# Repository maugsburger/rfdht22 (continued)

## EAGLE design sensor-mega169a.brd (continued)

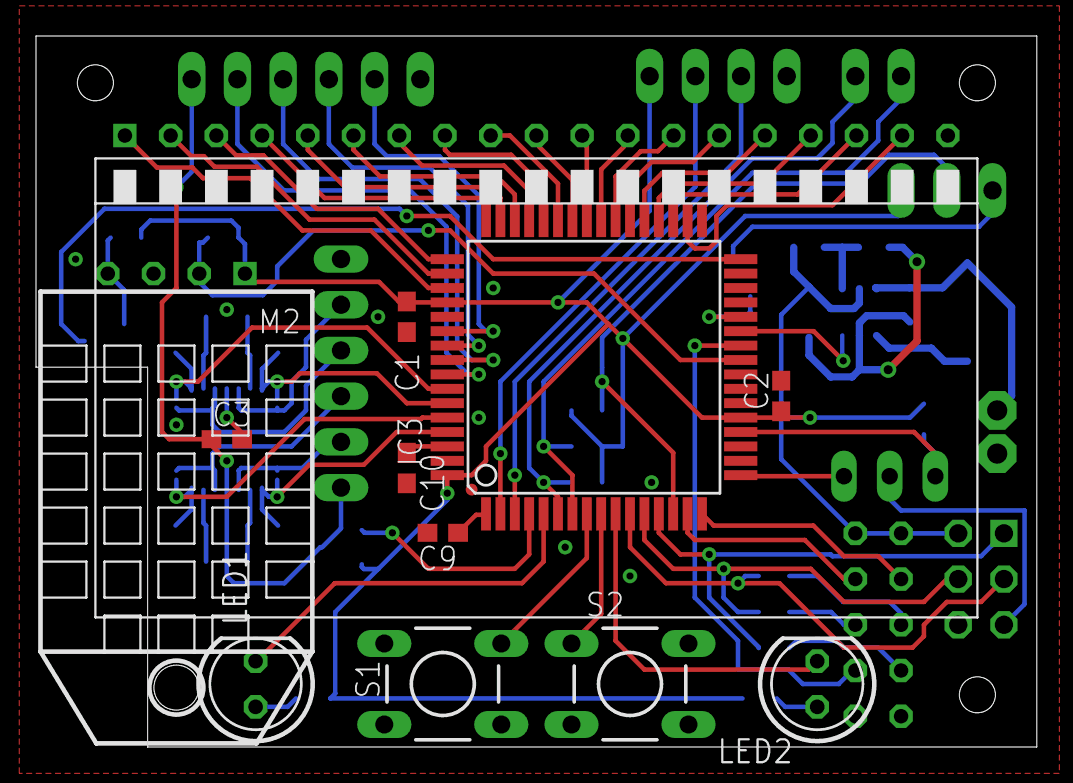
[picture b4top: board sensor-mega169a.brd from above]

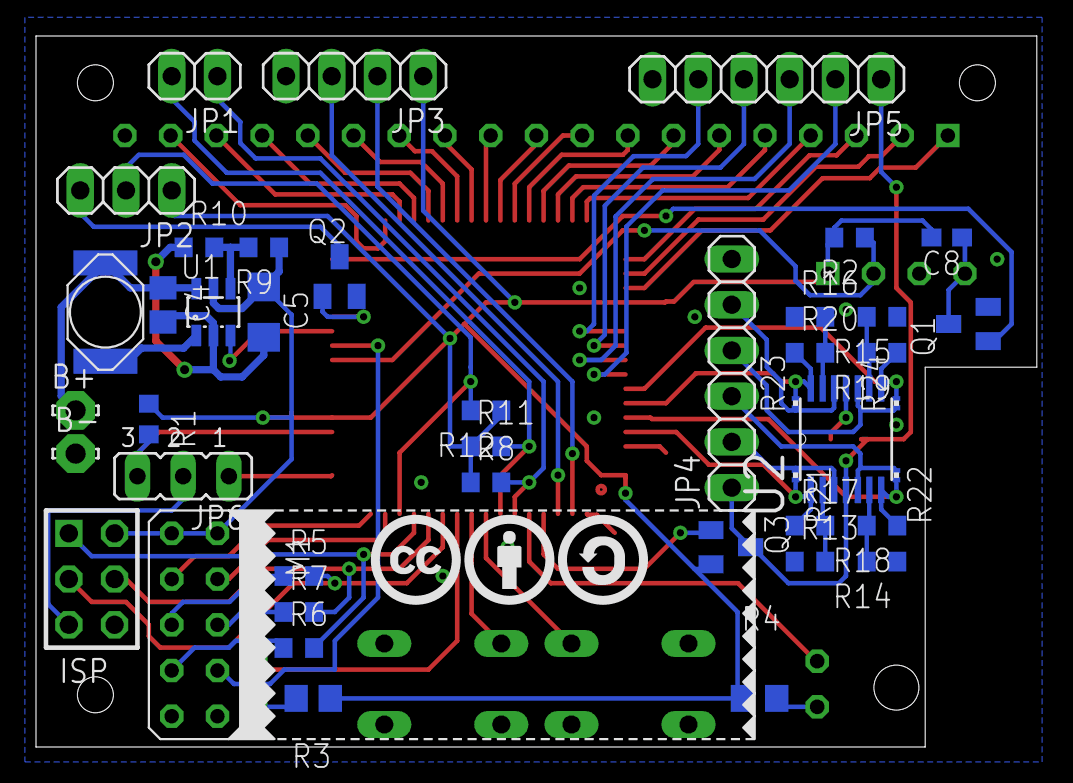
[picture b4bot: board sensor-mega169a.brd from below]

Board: 2 copper layers, 55.6 x 39.5 mm, 59 parts (46 on the bottom side), 72 nets.

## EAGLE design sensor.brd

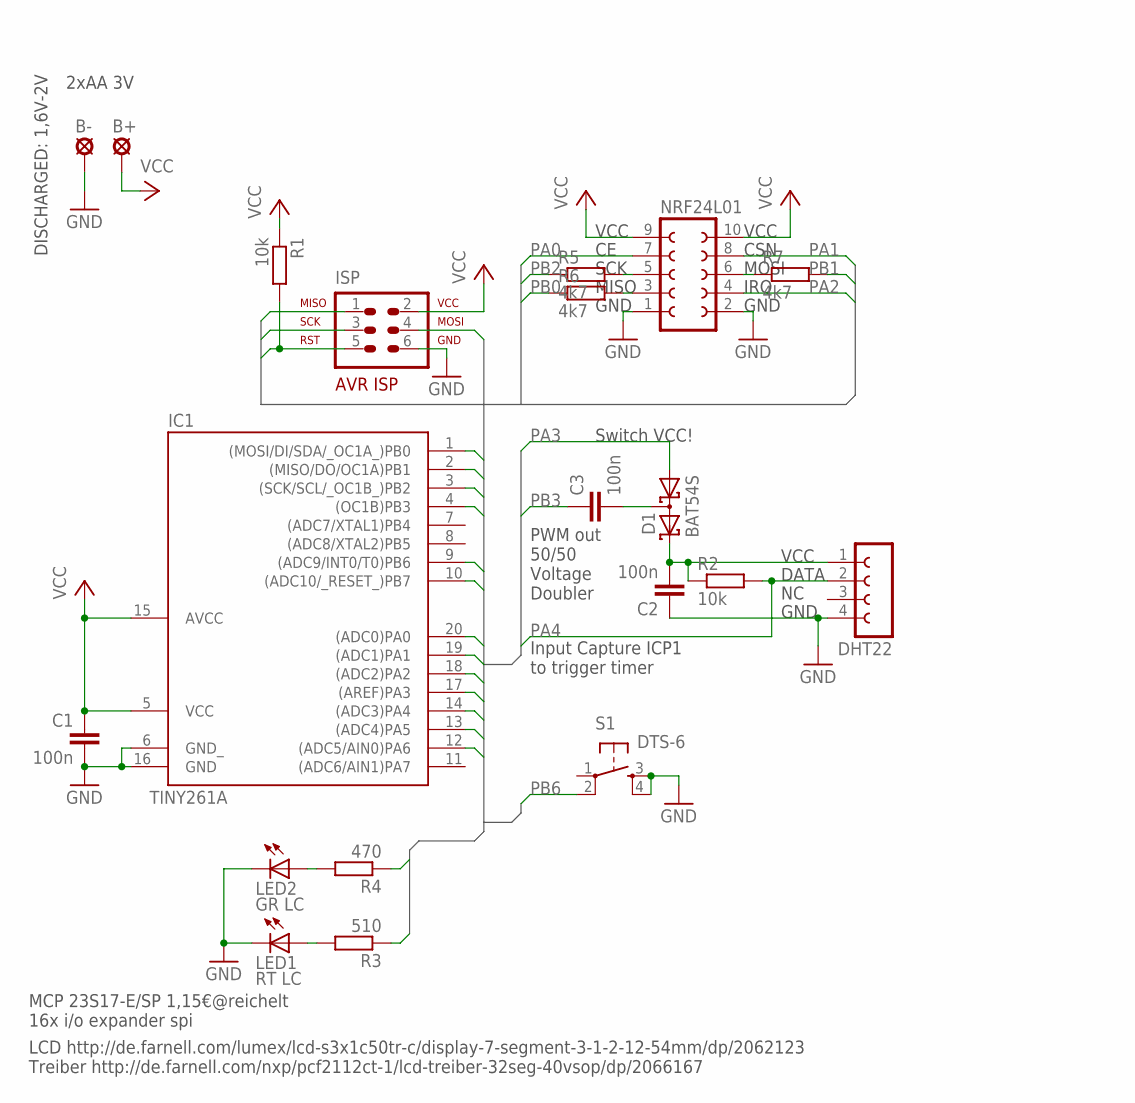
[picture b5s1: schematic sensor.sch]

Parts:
B+: LSP11
B-: LSP11
C1, C2, C3: 100n; C0805
D1: BAT54S; SOT23
DHT22: FE04-1
IC1: TINY261A; DIL20
ISP: ML6; AVR-ISP-6
LED1: RT LC; LED5MM
LED2: GR LC; LED5MM
NRF24L01: FE05-2
R1, R2: 10k; R0805
R3: 510; R0805
R4: 470; R0805
R5, R6, R7: 4k7; 0207/7
S1: DTS-6

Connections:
DHTVCC: C2.2, D1.2 (C2), DHT22.1, R2.1
GND: B-.MP, C1.2, C2.1, DHT22.4, IC1.6 (GND_), IC1.16 (GND), ISP.6, LED1.K (C), LED2.K (C), NRF24L01.1, NRF24L01.2, S1.3, S1.4
unnamed: LED2.A, R4.2
unnamed: C3.2, D1.3 (C1A2)
unnamed: NRF24L01.5, R5.2
unnamed: NRF24L01.3, R6.2
unnamed: NRF24L01.6, R7.1
unnamed: LED1.A, R3.2
PA0: IC1.20 ((ADC0)PA0), NRF24L01.7
PA1: IC1.19 ((ADC1)PA1), NRF24L01.8
PA2: IC1.18 ((ADC2)PA2), NRF24L01.4
PA3: D1.1 (A1), IC1.17 ((AREF)PA3)
PA4: DHT22.2, IC1.14 ((ADC3)PA4), R2.2
PA5: IC1.13 ((ADC4)PA5), R3.1
PA6: IC1.12 ((ADC5/AIN0)PA6), R4.1
PB0: IC1.1 ((MOSI/DI/SDA/_OC1A_)PB0), ISP.4, R6.1
PB1: IC1.2 ((MISO/DO/OC1A)PB1), ISP.1, R7.2
PB2: IC1.3 ((SCK/SCL/_OC1B_)PB2), ISP.3, R5.1
PB3: C3.1, IC1.4 ((OC1B)PB3)
PB6: IC1.9 ((ADC9/INT0/T0)PB6), S1.2
PB7: IC1.10 ((ADC10/_RESET_)PB7), ISP.5, R1.2
VCC: B+.MP, C1.1, IC1.5 (VCC), IC1.15 (AVCC), ISP.2, NRF24L01.9, NRF24L01.10, R1.1

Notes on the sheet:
VCC
SCK
GND
IRQ
MISO
MOSI
CSN
2xAA 3V
DATA
DISCHARGED: 1,6V-2V
Input Capture ICP1 to trigger timer
PWM out 50/50 Voltage Doubler
Switch VCC!
LCD http://de.farnell.com/lumex/lcd-s3x1c50tr-c/display-7-segment-3-1-2-12-54mm/dp/2062123 Treiber http://de.farnell.com/nxp/pcf2112ct-1/lcd-treiber-32seg-40vsop/dp/2066167
MCP 23S17-E/SP 1,15€@reichelt 16x i/o expander spi

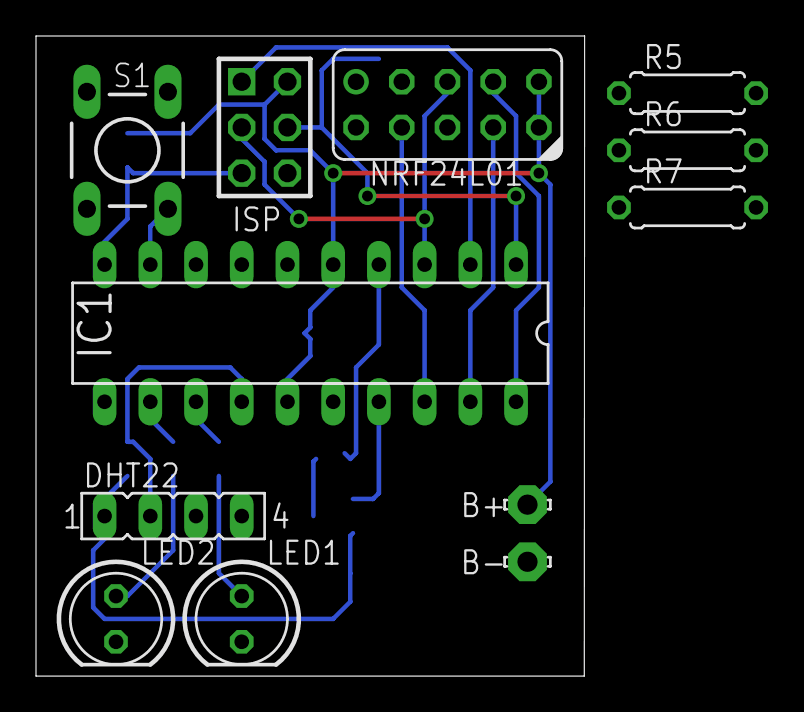
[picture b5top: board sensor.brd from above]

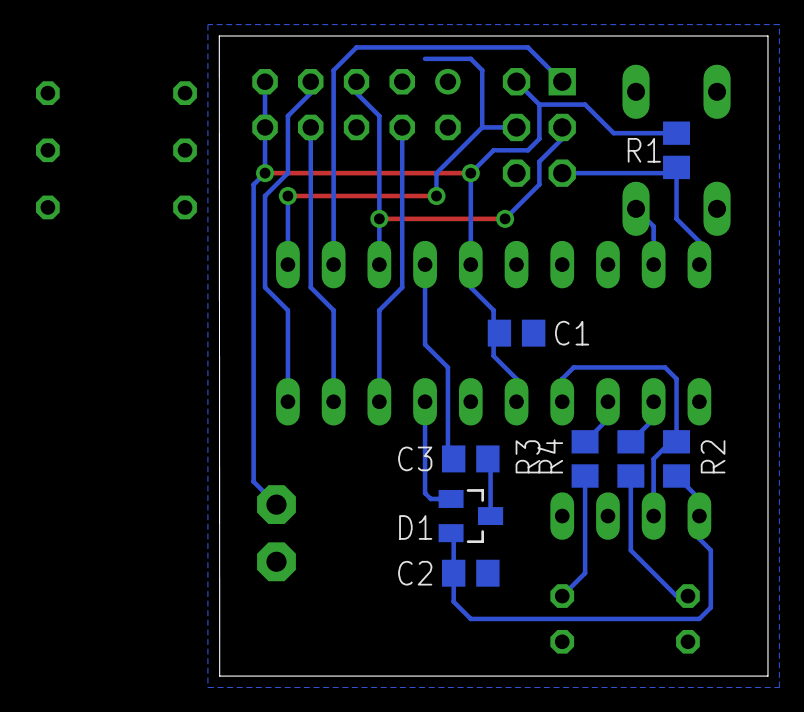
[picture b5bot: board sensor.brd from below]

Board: 2 copper layers, 30.5 x 35.6 mm, 20 parts (8 on the bottom side), 22 nets.

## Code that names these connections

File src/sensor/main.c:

/*
 * Copyright 2013 Moritz Augsburger <code@moritz.augsburger.name>
 *
 * This file is part of rfdht22.
 *
 * rfdht22 is free software: you can redistribute it and/or modify
 * it under the terms of the GNU General Public License as published by
 * the Free Software Foundation, either version 3 of the License, or
 * (at your option) any later version.
 *
 * Foobar is distributed in the hope that it will be useful,
 * but WITHOUT ANY WARRANTY; without even the implied warranty of
 * MERCHANTABILITY or FITNESS FOR A PARTICULAR PURPOSE.  See the
 * GNU General Public License for more details.
 *
 * You should have received a copy of the GNU General Public License
 * along with Foobar.  If not, see <http://www.gnu.org/licenses/>.
 *
 */

#include "main.h"
volatile uint8_t isr_interval;

void dhtpwr_on() {
        // PB2 == OC0A
        TCCR0A =    (1<<WGM01) | (1<<WGM00) | //
                    (1<<COM0A1); // Clear OC0A on match, set at TOP
        TCCR0B = (0<<CS01) | (1<<CS00); // no prescaling
        OCR0A = 127;

        // PB2 und PB0 Ausgang
        DDRB |= (1<<PB2) | (1<<PB0);
        // PB0 VCC für Doubler
        PORTB |= (1<<PB0);
}

void dhtpwr_off() {
        // PB2 und PB1 kein Ausgang
        PORTB &= ~(1<<PB0);
        DDRB &= ~(1<<PB2) | (1<<PB0);
        TCCR0A = (0<<WGM01) | (0<<WGM00);
        TCCR0B = (0<<CS01) | (0<<CS00);     // stop counter
}

void sleep_time(uint8_t sleepmode, uint8_t intervals ) {
    wdt_reset();
    isr_interval = intervals;
    WDTCR = (1<<WDIF) | (1<<WDIE) | (1<<WDP3) | (1<<WDP0);
    while(isr_interval > 0) {
        set_sleep_mode(sleepmode);
        sleep_mode();
    }
    wdt_disable();
}

void blink(uint8_t c) {
    do {
        PORTA |= (1<<PA0);
        _delay_ms(100);
        PORTA &= ~(1<<PA0);
        _delay_ms(100);
        c--;
    } while (c>0);
    _delay_ms(500);
}

int main (void) {

    uint16_t temperature;
    uint16_t humidity;
    uint8_t  dht22res;

    uint8_t payload[wl_module_PAYLOAD];		//Array for Payload
	uint8_t k;
	
	wl_module_init();	    //initialise nRF24L01+ Module
	_delay_ms(50);		    //wait for nRF24L01+ Module
    wl_module_tx_config(wl_module_TX_NR_0);		//Config Module

 //   dhtpwr(true);

    PORTA = (1<<PA1) | (1<<PA0);
    DDRA  = (1<<PA0) | (1<<PA1);
    _delay_ms(500);

    while(1) {
        // measure
        PORTA = (1<<PA1);
        dht22res = dhtmeasure(&temperature, &humidity );
        PORTA = 0;

        for (k=0; k<=wl_module_PAYLOAD-1; k++) {
            payload[k] = k;
        }
        payload[0] = dht22res;
        payload[1] = temperature;
        payload[2] = (temperature>>8);
        payload[3] = humidity;
        payload[4] = (humidity>>8);

        sei();
        wl_module_send(payload,wl_module_PAYLOAD);
        _delay_ms(5000);

    }
}

ISR(WDT_OVERFLOW_vect) {
    isr_interval--; 
}

#if defined(__AVR_ATtiny2313__) || defined(__AVR_ATtiny2313A__)
ISR(INT0_vect) {
#endif
    uint8_t status;

    // Read wl_module status
    wl_module_CSN_lo;                               // Pull down chip select
    status = spi_fast_shift(NOP);					// Read status register
    wl_module_CSN_hi;                               // Pull up chip select

    // Package has been sent
    if (status & (1<<TX_DS)) {
        wl_module_config_register(STATUS, (1<<TX_DS));	//Clear Interrupt Bit
        PTX=0;
    }

    // IRQ: Package has not been sent, send again
    if (status & (1<<MAX_RT)) {
        wl_module_config_register(STATUS, (1<<MAX_RT));	// Clear Interrupt Bit
        wl_module_CE_hi;								// Start transmission
        _delay_us(10);								
        wl_module_CE_lo;
    }

    //TX_FIFO Full <-- this is not an IRQ
    if (status & (1<<TX_FULL)) {
        wl_module_CSN_lo;                               // Pull down chip select
        spi_fast_shift(FLUSH_TX);						// Flush TX-FIFO
        wl_module_CSN_hi;                               // Pull up chip select
    }
}
/*
static volatile uint8_t zahl[5];

        asm (   "sec"       "\n\t"
                "rol %0"    "\n\t"
                "rol %1"    "\n\t"
                "rol %2"    "\n\t"
                "rol %3"    "\n\t"
                "rol %4"
                :"+r"( zahl[4] ),
                 "+r"( zahl[3] ),
                 "+r"( zahl[2] ),
                 "+r"( zahl[1] ),
                 "+r"( zahl[0] ) );

=> 26 zyklen
*/

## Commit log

2013-06-21 started project
2013-06-25 dht22 measurement and serial output working
2013-06-25 nrf24l01 code from http://www.mikrocontroller.net/articles/NRF24L01_Tutorial
2013-06-25 import lcd lib from http://homepage.hispeed.ch/peterfleury/avr-software.html
2013-06-25 first draft of master circuit
2013-06-26 fileencoding, strict prototype warnings
2013-06-26 fix warning about KS0073_4LINES_MODE
2013-06-27 use cpu clock defined in F_CPU
2013-06-27 moved dht22 and uart to external libs
2013-06-27 use externalized uart/dht22 libs
2013-06-27 start uc specific code – attiny2313
2013-06-27 added watch crystal to master, notes for sensor
2013-06-27 compile libs, lib config
2013-06-27 switch to 2313a for nicer header io definitions
2013-06-27 gnararghs, missing crttn2313a.o, easy fix
2013-06-28 remove unused module functions
2013-06-29 init function
2013-06-29 no SS in spi-lib, code formating
2013-06-29 added spi for usi on attiny2313(a)
2013-06-29 file format unix
2013-06-29 move pin definitions from lib to project
2013-06-29 6 byte payload are enough atm
2013-06-29 attiny2313 int0 config
2013-06-29 trailing white spaces removed
2013-06-29 successfully sending
2013-06-29 recieving and data dumping master working
2013-06-29 di == miso, do == mosi for usi in spi mode
2013-06-30 thoughts about connecting an lcd
2013-07-01 series resistors for shared spi/isp interface
2013-07-02 some more ideas whta to implement in future
2013-07-04 switch sensor to attiny2313a
2013-07-06 deluxe sensor board with lcd and everything
2013-07-07 removed really complicating lcd from small version, layouted single sided pcb
2013-07-07 outdated pin config, no double usage now -> can be removed
2013-07-07 changed irlml* parts to own library with better footprint
2013-07-08 rf protocol and eeprom design thoughts
2013-07-08 fixed table, rearranged protocol to fit data/config/new_sensor
2013-07-08 renamed markdown files with correct extension
2013-07-08 really simple config protocol, but enough for the moment
2013-07-08 atmega1284 is pin compatible
2013-07-08 removed useless layers
2013-07-08 use attiny2313_a_, upload eeprom
2013-07-08 split dhtpwr in two seperate functions
2013-07-08 sleep mode handling function
2013-07-08 create proper header file with prototypes
2013-07-08 cc-by-sa license
2013-07-08 added jumper for spi slave extensions on isp header
2013-07-08 icp timing for dht22 at 4MHz, ISR might be too slow, though
2013-07-08 power up function
2013-07-09 rearranged some wires
2013-07-09 hanged to xmega, better performance at lower price
2013-07-10 some rerouting
2013-07-12 added forgotten lan interface
2013-07-13 improved spacing between some layers
2013-07-13 sensor-xmega3 top+bottom silk screen arranged
2013-07-13 updated usb socket device
2013-07-13 quadrature decoder needs two successive pins for input -> swapped s1
2013-07-14 changed dru to mm, measured lan socket
2013-07-14 changed dru, width and drills to oshpark (finer pitch)
2013-07-14 added license+version information
2013-07-14 +5V also in netclass power with bigger width
2013-07-14 improved routing
2013-07-14 moved x3 to the right
2013-07-15 added sd card interface
2013-07-15 oshw logo, drc errors fixed
2013-07-16 auto creation of images
2013-07-16 further pcb/schem images
2013-07-16 moved some parts to test image diff
2013-07-16 moved silk prints off from pads
2013-07-16 fix images
2013-07-16 moved SG1, more clearance around pdi
2013-07-16 0603 and sot23 got silk screen
2013-07-17 decoupling cap for rtc
2013-07-17 lcd connector changed to standard 2.54 pin header
2013-07-18 attiny so20 package
2013-07-18 deleted second sch sheet with case scribbling
2013-07-18 renamed ic1->u1, u1->u2
2013-07-18 GPL3 license text
2013-07-18 gpl licensed according to http://homepage.hispeed.ch/peterfleury/avr-software.html
2013-07-18 MIT style license, added author
2013-07-18 gpl headers for all self created files
2013-07-18 CC-BY-SA for schematics and boards
2013-07-20 dht22 sometimes hang, add mosfet as low side reset switch
2013-07-20 logo, first draft
2013-11-06 gnd plane reshaped
2014-02-24 pulldown for boostup enable line
2014-08-04 problems with first prototype
2014-08-04 free seg14/15, can't be used with lcd in use
2014-08-04 reassign display pins
    fixes #1
